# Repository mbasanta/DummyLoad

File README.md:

# DummyLoad

KiCad project for a 50 ohm RF dummy load board with integrated attenuation and rectified measurement output.

## Overview

This repository contains the schematic, PCB, custom footprint library, and generated manufacturing artifacts for the DummyLoad board.

From the schematic title block and notes:
- Design target: 50 ohm dummy load
- Rated power (design intent): 10 W
- Includes attenuation network:
  - Note in schematic: "40db Attenuation (use 3x 261 Ohm resistors for 30db)"
- Includes a rectified voltage measurement point for RF power estimation (see [Dummy Load Voltages](output/Dummy%20Load%20Voltages.pdf) for the relationship between rectified voltage and radio power output)

## Schematic

## PCB

## Main Files

- `DummyLoad.kicad_sch`: KiCad schematic
- `DummyLoad.kicad_pcb`: KiCad PCB layout
- `DummyLoad.kicad_pro`: KiCad project
- `MiscFootprints.pretty/`: Local footprint library used by this project
- `output/`: Generated artifacts (BOM, schematic PDF, Gerbers, drill files)
- `.github/workflows/kicad.yml`: CI workflow for ERC/DRC and artifact generation

## Connectors and Test Points

- `J1`: RF In (BNC horizontal)
- `J2`: RF Out (BNC horizontal)
- `TP1`: Power Out (rectified measurement output)
- `TP2`: GND

## Bill of Materials

A generated BOM is committed at:
- `output/bom.csv`

The CI workflow exports BOM fields:
- Reference
- Value
- Footprint
- Quantity
- DNP
- Mouser PN
- Datasheet

## Generated Manufacturing Outputs

When CI succeeds, generated files are updated in:
- `output/schematic.pdf`
- `output/bom.csv`
- `output/gerbers/`

These include copper, mask, silkscreen, fab, edge cuts, and drill outputs.

## CI / Automation

GitHub Actions workflow: `.github/workflows/kicad.yml`

It runs on pushes and pull requests to `main` (ignoring changes under `output/**`) and can also be triggered manually.

The workflow performs:
1. KiCad ERC
2. KiCad DRC
3. Schematic PDF export
4. BOM export
5. Gerber and drill export
6. Commit updated generated outputs on `main`
7. Upload production artifacts

## Working With the Project Locally

1. Open `DummyLoad.kicad_pro` in KiCad.
2. Ensure the local footprint library is available:
   - `MiscFootprints.pretty`
3. Run:
   - Schematic Editor ERC
   - PCB Editor DRC
4. Generate fabrication outputs from KiCad if needed.

## Safety and Validation Notes

This project handles RF power dissipation. Before physical use:
- Verify resistor power dissipation and thermal limits for your operating conditions.
- Validate attenuation and measurement calibration on your target frequency range.
- Confirm connector, PCB copper, and assembly choices meet your power and duty-cycle requirements.

## License

MIT. See `LICENSE`.

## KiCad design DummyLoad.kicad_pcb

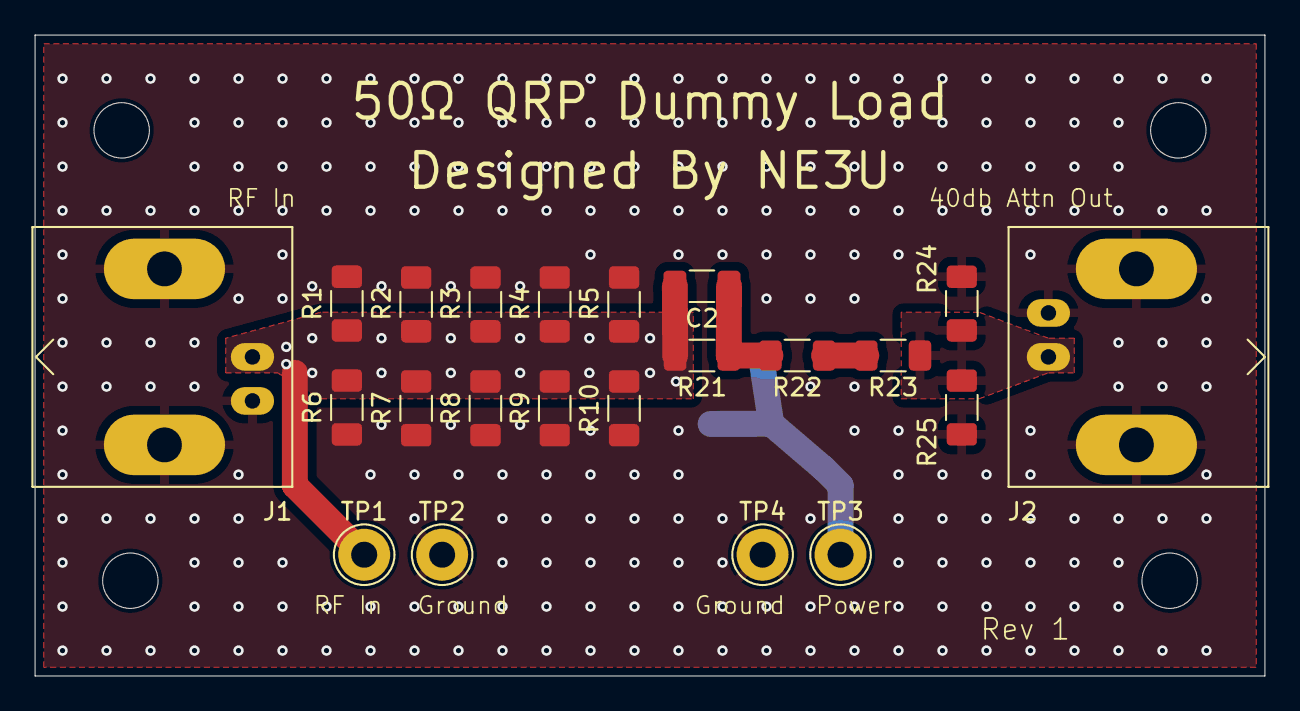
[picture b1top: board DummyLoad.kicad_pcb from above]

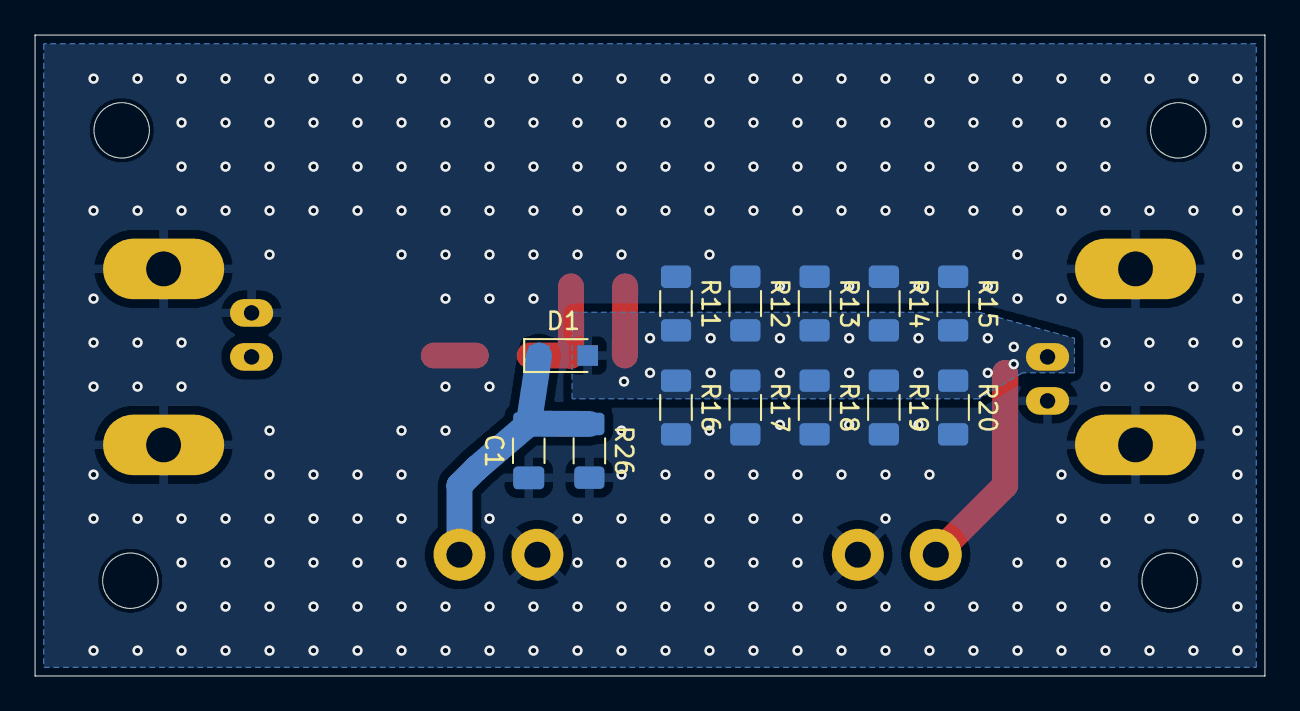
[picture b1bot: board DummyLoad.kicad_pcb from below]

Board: 2 copper layers, 71.0 x 37.0 mm, 39 parts (13 on the bottom side), 6 nets.

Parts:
C1: 10nF; C_1206_3216Metric_Pad1.33x1.80mm_HandSolder
C2: C; C_1206_3216Metric_Pad1.33x1.80mm_HandSolder
D1: 1N5711; Nexperia_CFP3_SOD-123W
H1, H2, H3, H4: MountingHole_Pad; MountingHole_3.2mm_M3
J1: RF In; BNC_Amphenol_B6252HB-NPP3G-50_Horizontal
J2: RF Out; BNC_Amphenol_B6252HB-NPP3G-50_Horizontal
R1, R2, R3, R4, R5, R6, R7, R8, R9, R10, R11, R12, R13, R14, R15, R16, R17, R18, R19, R20: 1K; R_1206_3216Metric_Pad1.30x1.75mm_HandSolder
R21, R22, R23: 820; R_1206_3216Metric_Pad1.30x1.75mm_HandSolder
R24, R25: 102; R_1206_3216Metric_Pad1.30x1.75mm_HandSolder
R26: 100K; R_1206_3216Metric_Pad1.30x1.75mm_HandSolder
TP1: RF In; TestPoint_THTPad_D3.0mm_Drill1.5mm
TP2, TP4: GND; TestPoint_THTPad_D3.0mm_Drill1.5mm
TP3: Power Out; TestPoint_THTPad_D3.0mm_Drill1.5mm

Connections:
GND: C1.2, J1.2 (Ext), J2.2 (Ext), R1.2, R2.2, R3.2, R4.2, R5.2, R6.2, R7.2, R8.2, R9.2, R10.2, R11.2, R12.2, R13.2, R14.2, R15.2, R16.2, R17.2, R18.2, R19.2, R20.2, R24.2, R25.2, R26.2, TP2.1, TP4.1
unnamed: C2.1, R21.1, R22.2
unnamed: C1.1, D1.1 (K), R26.1, TP3.1
unnamed: R22.1, R23.2
RF_In: C2.2, D1.2 (A), J1.1 (In), R1.1, R2.1, R3.1, R4.1, R5.1, R6.1, R7.1, R8.1, R9.1, R10.1, R11.1, R12.1, R13.1, R14.1, R15.1, R16.1, R17.1, R18.1, R19.1, R20.1, R21.2, TP1.1
RF_Out: J2.1 (In), R23.1, R24.1, R25.1

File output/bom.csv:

"Refs","Value","Footprint","Qty","DNP","Mouser PN","Datasheet"
"C1","10nF","Capacitor_SMD:C_1206_3216Metric_Pad1.33x1.80mm_HandSolder","1","","77-VJ1206Y103JXAMP","https://www.vishay.com/docs/45199/vjcommercialseries.pdf"
"C2","C","Capacitor_SMD:C_1206_3216Metric_Pad1.33x1.80mm_HandSolder","1","DNP","","~"
"D1","1N5711","Diode_SMD:Nexperia_CFP3_SOD-123W","1","","621-1N5711W-F","https://www.mouser.com/datasheet/3/175/1/1N5711W.pdf"
"J1","RF In","Connector_Coaxial:BNC_Amphenol_B6252HB-NPP3G-50_Horizontal","1","","737-RF101KD0050BKHDW ","https://www.mouser.com/datasheet/3/6015/1/rf1_01k_d_00_50_bk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"
"J2","RF Out","Connector_Coaxial:BNC_Amphenol_B6252HB-NPP3G-50_Horizontal","1","","737-RF101KD0050BKHDW","https://www.mouser.com/datasheet/3/6015/1/rf1_01k_d_00_50_bk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"
"R1","1K","Resistor_SMD:R_1206_3216Metric_Pad1.30x1.75mm_HandSolder","1","","71-RCS12061K00FKEA","https://www.vishay.com/docs/20065/rcse3.pdf"
"R2","1K","Resistor_SMD:R_1206_3216Metric_Pad1.30x1.75mm_HandSolder","1","","71-RCS12061K00FKEA","https://www.vishay.com/docs/20065/rcse3.pdf"
"R3","1K","Resistor_SMD:R_1206_3216Metric_Pad1.30x1.75mm_HandSolder","1","","71-RCS12061K00FKEA","https://www.vishay.com/docs/20065/rcse3.pdf"
"R4","1K","Resistor_SMD:R_1206_3216Metric_Pad1.30x1.75mm_HandSolder","1","","71-RCS12061K00FKEA","https://www.vishay.com/docs/20065/rcse3.pdf"
"R5","1K","Resistor_SMD:R_1206_3216Metric_Pad1.30x1.75mm_HandSolder","1","","71-RCS12061K00FKEA","https://www.vishay.com/docs/20065/rcse3.pdf"
"R6","1K","Resistor_SMD:R_1206_3216Metric_Pad1.30x1.75mm_HandSolder","1","","71-RCS12061K00FKEA","https://www.vishay.com/docs/20065/rcse3.pdf"
"R7","1K","Resistor_SMD:R_1206_3216Metric_Pad1.30x1.75mm_HandSolder","1","","71-RCS12061K00FKEA","https://www.vishay.com/docs/20065/rcse3.pdf"
"R8","1K","Resistor_SMD:R_1206_3216Metric_Pad1.30x1.75mm_HandSolder","1","","71-RCS12061K00FKEA","https://www.vishay.com/docs/20065/rcse3.pdf"
"R9","1K","Resistor_SMD:R_1206_3216Metric_Pad1.30x1.75mm_HandSolder","1","","71-RCS12061K00FKEA","https://www.vishay.com/docs/20065/rcse3.pdf"
"R10","1K","Resistor_SMD:R_1206_3216Metric_Pad1.30x1.75mm_HandSolder","1","","71-RCS12061K00FKEA","https://www.vishay.com/docs/20065/rcse3.pdf"
"R11","1K","Resistor_SMD:R_1206_3216Metric_Pad1.30x1.75mm_HandSolder","1","","71-RCS12061K00FKEA","https://www.vishay.com/docs/20065/rcse3.pdf"
"R12","1K","Resistor_SMD:R_1206_3216Metric_Pad1.30x1.75mm_HandSolder","1","","71-RCS12061K00FKEA","https://www.vishay.com/docs/20065/rcse3.pdf"
"R13","1K","Resistor_SMD:R_1206_3216Metric_Pad1.30x1.75mm_HandSolder","1","","71-RCS12061K00FKEA","https://www.vishay.com/docs/20065/rcse3.pdf"
"R14","1K","Resistor_SMD:R_1206_3216Metric_Pad1.30x1.75mm_HandSolder","1","","71-RCS12061K00FKEA","https://www.vishay.com/docs/20065/rcse3.pdf"
"R15","1K","Resistor_SMD:R_1206_3216Metric_Pad1.30x1.75mm_HandSolder","1","","71-RCS12061K00FKEA","https://www.vishay.com/docs/20065/rcse3.pdf"
"R16","1K","Resistor_SMD:R_1206_3216Metric_Pad1.30x1.75mm_HandSolder","1","","71-RCS12061K00FKEA","https://www.vishay.com/docs/20065/rcse3.pdf"
"R17","1K","Resistor_SMD:R_1206_3216Metric_Pad1.30x1.75mm_HandSolder","1","","71-RCS12061K00FKEA","https://www.vishay.com/docs/20065/rcse3.pdf"
"R18","1K","Resistor_SMD:R_1206_3216Metric_Pad1.30x1.75mm_HandSolder","1","","71-RCS12061K00FKEA","https://www.vishay.com/docs/20065/rcse3.pdf"
"R19","1K","Resistor_SMD:R_1206_3216Metric_Pad1.30x1.75mm_HandSolder","1","","71-RCS12061K00FKEA","https://www.vishay.com/docs/20065/rcse3.pdf"
"R20","1K","Resistor_SMD:R_1206_3216Metric_Pad1.30x1.75mm_HandSolder","1","","71-RCS12061K00FKEA","https://www.vishay.com/docs/20065/rcse3.pdf"
"R21","820","Resistor_SMD:R_1206_3216Metric_Pad1.30x1.75mm_HandSolder","1","","279-CRGH1206F820R","https://www.te.com/commerce/DocumentDelivery/DDEController?A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"
"R22","820","Resistor_SMD:R_1206_3216Metric_Pad1.30x1.75mm_HandSolder","1","","279-CRGH1206F820R","https://www.te.com/commerce/DocumentDelivery/DDEController?A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"
"R23","820","Resistor_SMD:R_1206_3216Metric_Pad1.30x1.75mm_HandSolder","1","","279-CRGH1206F820R","https://www.te.com/commerce/DocumentDelivery/DDEController?A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"
"R24","102","Resistor_SMD:R_1206_3216Metric_Pad1.30x1.75mm_HandSolder","1","","667-ERJ-8ENF1020V","https://industrial.panasonic.com/cdbs/www-data/pdf/RDO0000/R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"
"R25","102","Resistor_SMD:R_1206_3216Metric_Pad1.30x1.75mm_HandSolder","1","","667-ERJ-8ENF1020V","https://industrial.panasonic.com/cdbs/www-data/pdf/RDO0000/R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"
"R26","100K","Resistor_SMD:R_1206_3216Metric_Pad1.30x1.75mm_HandSolder","1","","652-CRM1206QFX-1003E","https://www.mouser.com/catalog/specsheets/Bourns_1-11-2023_C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"
"TP1","RF In","TestPoint:TestPoint_THTPad_D3.0mm_Drill1.5mm","1","","","~"
"TP2","GND","TestPoint:TestPoint_THTPad_D3.0mm_Drill1.5mm","1","","","~"
"TP3","Power Out","TestPoint:TestPoint_THTPad_D3.0mm_Drill1.5mm","1","","","~"
"TP4","GND","TestPoint:TestPoint_THTPad_D3.0mm_Drill1.5mm","1","","","~"

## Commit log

2026-03-24 Add DummyLoad KiCad project and footprints
    Add a new KiCad project for a DummyLoad: DummyLoad.kicad_pcb, DummyLoad.kicad_pro, and DummyLoad.kicad_sch. Includes PCB layout with BNC connector, resistor footprints, mounting holes and pin header;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
2026-03-24 Add KiCad workflow for production file generation
2026-03-24 Modify production file paths in kicad.yml
    Updated file paths for production files in KiCad workflow.
2026-03-24 Schematic: add symbols, ground & rewire
    Modify DummyLoad.kicad_sch: add new symbols and power net, reposition several components and update wiring/junctions. Added Device:R_US instances (R24, R23), a power:GND symbol that creates a global 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
2026-03-24 Update KiCad workflow to ignore output paths
2026-03-24 chore(kicad): update generated outputs [skip ci]
2026-03-24 Update .gitignore to remove BOM file exclusions
    Remove BOM file patterns from .gitignore
2026-03-24 Add BOM fields and labels to KiCad workflow
2026-03-24 Fix BOM fields and labels formatting in kicad.yml
2026-03-24 Refactor KiCad GitHub Actions workflow
    Updated KiCad workflow to improve output handling and error checking.
2026-03-24 Update KiCad GitHub Actions workflow
    Updated KiCad workflow to use actions/checkout@v6 and modified output file handling.
2026-03-24 Rename pcb_file to pcb_file_name in kicad.yml
2026-03-24 Disable DRC check in kicad.yml
    Temporarily disable DRC check in KiCad workflow.
2026-03-24 Fix copy commands and update GitHub Action version
2026-03-24 Remove drill output from workflow
    Removed drill directory from output copying and git add.
2026-03-24 Schematic: update layout & title block
    Set paper to USLetter and add a title block (title, date, revision, company and descriptive comments). Perform a large schematic redraw: many junctions, wires and their coordinates were moved and mul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
2026-03-26 Refactor connector, testpoints and layout
    Replace generic connector symbols with coaxial/TestPoint symbols and tidy schematic metadata; adjust component positions, wires and junctions, and update footprints/datasheets/Mouser PNs. Added text 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
2026-03-26 Add THT test point footprints to schematic
    Assign the TestPoint footprint to two components in DummyLoad.kicad_sch. Previously the Footprint property was empty; this commit sets it to "TestPoint:TestPoint_THTPad_D1.0mm_Drill0.5mm" for the two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
2026-03-26 Update component datasheets, PNs, footprints
    Update metadata in DummyLoad.kicad_sch: replace generic Vishay datasheet links with the direct rcse3.pdf URL and change Mouser PN from 279-CRGP2512F1K0 to 71-RCS12061K00FKEA across multiple component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
2026-03-26 Update PCB footprints, add test points and enable DRC
    Enable run_drc in the GitHub workflow and apply extensive footprint changes in DummyLoad.kicad_pcb: add THT test points, convert multiple resistors from 2512 to 1206 footprints (position/size/pad upd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
2026-03-26 Add README for DummyLoad KiCad project
    Add a comprehensive README documenting the DummyLoad KiCad project: design targets (50 Ω dummy load, 10 W), included files (schematic, PCB, footprints, outputs), connectors/test points, BOM location,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
2026-03-26 Change diode value to 1N5711
    Update the diode 'Value' property from 1N4004 to 1N5711 in both the KiCad schematic and PCB files (DummyLoad.kicad_sch and DummyLoad.kicad_pcb) so the schematic and board reflect the new component se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
2026-03-26 Upload KiCad ERC/DRC diagnostics on failure
    When the KiCad production step fails, collect common ERC/DRC/report/log files from the workspace into a diagnostics/ directory and upload them as an artifact (actions/upload-artifact@v7). Uses a find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
2026-03-26 Remove generated gerber output files
    Delete generated DummyLoad gerber and drill outputs under output/gerbers (including nested output/gerbers/gerbers). These are PCB fabrication artifacts (Gerber, drill, job files) and are being remove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
2026-03-26 Copy gerbers to output and ignore .DS_Store
    Update CI workflow to copy the gerbers into the output directory (changed cp target from output/gerbers to output) so generated artifacts are placed directly under output. Also add .DS_Store to .giti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
2026-03-26 Update KiCad workflow and remove generated gerbers
    Add an explicit pcb_output_layers setting to .github/workflows/kicad.yml to control which PCB layers are exported by the KiCad CI step. Remove a large set of generated gerber/drill files from output/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
2026-03-26 Update DummyLoad.kicad_pcb polygon coords
    Adjust polygon and filled_polygon vertex coordinates in DummyLoad.kicad_pcb (F.Cu and B.Cu). Fixes corner vertex from x=168.5 to x=169 and normalizes several numeric precision values (e.g. 168.874259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
2026-03-28 Add BNC STEP model and update PCB
    Add 3dShapes/CONBNC002.stp — a STEP AP214 3D model (exported from SolidWorks 2021) for the BNC connector. Also update DummyLoad.kicad_pcb to reference the new 3D model so the connector is available f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
2026-03-28 Adjust BNC connector 3D model and pad UUIDs
    Update BNC connector footprint: set reference rotation from 180 to 0, add CONBNC002.stp 3D model with offset (0, 5.1, 0) and rotation (-90, 0, -180), and replace two pad UUIDs with new unique values.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
2026-03-29 Enable SVG outputs in KiCad workflow
    Add schematic_output_svg: true and pcb_output_svg: true to the .github/workflows/kicad.yml so the CI generates SVG exports for schematics and PCBs. This enables producing visual artifacts useful for 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
2026-03-29 Include SVG outputs in CI artifacts
    Copy schematic and PCB SVGs into the output directory and include them in the committed/uploaded artifacts. The workflow now copies schematics/DummyLoad.svg -> output/schematic.svg and pcb.svg -> out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
2026-03-29 Use PNG for PCB output in CI workflow
    Switch the KiCad GitHub Actions workflow to produce PCB output as an image (png) instead of SVG by enabling pcb_output_image and updating file copy/upload steps. Adjusted artifact paths and collectio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
2026-03-29 Update KiCad workflow outputs; remove pcb.svg
    Add additional PCB image outputs in .github/workflows/kicad.yml (pcb_output_image_floor and pcb_oupput_image_perspective), update artifact staging to add output/pcb.png instead of output/pcb.svg, and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
2026-04-07 Add schematic SVG and pcb.png images to README
    Agent-Logs-Url: https://github.com/mbasanta/DummyLoad/sessions/f675b0ef-5048-4c67-9bc1-c7e1d741e8dc
2026-04-07 Move schematic and PCB sections to below Overview
    Agent-Logs-Url: https://github.com/mbasanta/DummyLoad/sessions/89c86934-170e-4b6b-88e9-e793920221af
2026-04-09 Enlarge THT test points and update PCB layout
    Replace TP1/TP2 footprints with larger THT test points (TestPoint_THTPad_D3.0mm_Drill1.5mm): pad sizes and drill diameters increased from 1.0/0.5mm to 3.0/1.5mm, and related silk/fab text positions a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
2026-04-09 Use hand-solder 1206 resistor footprints
    Replace Resistor_SMD:R_1206_3216Metric with R_1206_3216Metric_Pad1.30x1.75mm_HandSolder across the PCB. Pads enlarged from 1.125x1.75 to 1.30x1.75 (adjusted roundrect ratio) and pad positions/rotatio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
2026-04-09 Set zone_connect and fix text rotations
    Add zone_connect 2 to multiple SMD footprints/pads and components to enable zone connectivity. Update many property and fp_text rotations from 270° to 90° to correct silkscreen/fab text orientation. 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
2026-04-10 Add TH testpoints and update PCB labels/layout
    Add two through-hole testpoint footprints (RF In and GND) and reassign existing testpoint references (TP1/TP2 -> TP3/TP4). Adjusted testpoint coordinates and nets, updated multiple silkscreen texts (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
2026-04-10 Update schematic metadata and pin UUID
    Bump sheet date and revision, refine title-block comments to note best performance up to 30MHz and a QRP power rating, and correct a pin UUID (...29e -> ...29f). Documentation and identifier cleanup 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
2026-04-10 Adjust PCB testpoints, silks and via positions
    Update DummyLoad.kicad_pcb: shift two THT testpoint footprints (TP1, TP2) and nudge silk labels ("RF In", "Ground"). Repositioned many vias across the board and regenerated their UUIDs to match the n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
2026-04-10 Add rotation parameter for PCB output image
2026-04-10 Fix rotation angle for PCB output image
2026-04-10 Fix rotation angle in KiCad workflow
2026-04-10 Correct pcb_output_image_perspective and rotation
    Fix typo in pcb_output_image_perspective and update rotation values.
2026-04-10 Change PCB output image rotation parameters
2026-05-02 Add dummy load voltages PDF and update README
    Add output/Dummy Load Voltages.pdf documenting the relationship between rectified voltage and radio power output, and update README to reference the new PDF for details on the rectified voltage measu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
